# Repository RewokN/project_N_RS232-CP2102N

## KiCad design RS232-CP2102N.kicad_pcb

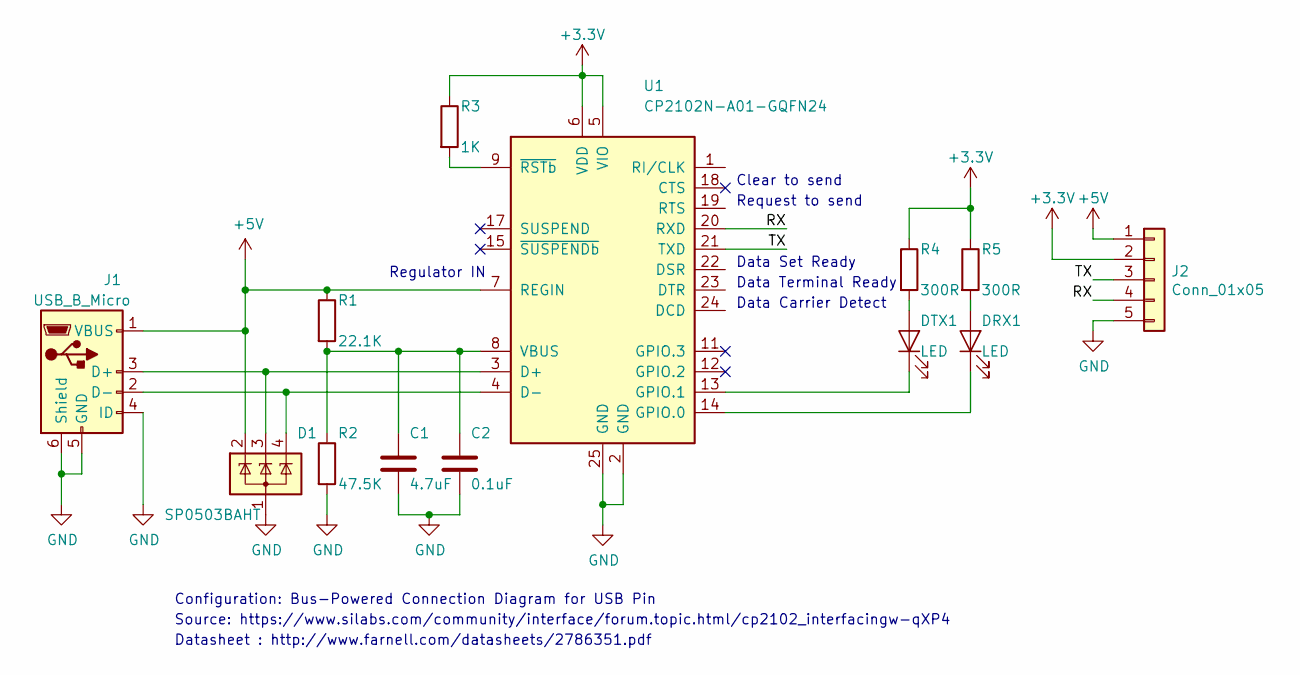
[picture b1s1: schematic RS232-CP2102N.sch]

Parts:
C1: 4.7uF; C_0805_2012Metric
C2: 0.1uF; C_0805_2012Metric
D1: SP0503BAHT; SOT-143
DRX1: LED; LED_0805_2012Metric
DTX1: LED; LED_0805_2012Metric
J1: USB_B_Micro; USB_Micro-B_Molex-105017-0001
J2: Conn_01x05; PinHeader_1x05_P2.54mm_Vertical
R1: 22.1K; R_0805_2012Metric
R2: 47.5K; R_0805_2012Metric
R3: 1K; R_0805_2012Metric
R4, R5: 300R; R_0805_2012Metric
U1: CP2102N-A01-GQFN24; QFN-24-1EP_4x4mm_P0.5mm_EP2.6x2.6mm

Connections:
+3V3: J2.2, R3.1, R4.1, R5.1, U1.5 (VIO), U1.6 (VDD)
+5V: D1.2 (K), J1.1 (VBUS), J2.1, R1.1, U1.7 (REGIN)
/RX: J2.4, U1.20 (RXD)
/TX: J2.3, U1.21 (TXD)
GND: C1.2, C2.2, D1.1 (A), J1.4 (ID), J1.5 (GND), J1.6 (Shield), J2.5, R2.2, U1.2 (GND), U1.25 (GND)
unnamed: C1.1, C2.1, R1.2, R2.1, U1.8 (VBUS)
unnamed: D1.3 (K), J1.3 (D+), U1.3 (D+)
unnamed: D1.4 (K), J1.2 (D-), U1.4 (D-)
unnamed: DRX1.1 (K), U1.14 (GPIO.0)
unnamed: DRX1.2 (A), R5.2
unnamed: DTX1.1 (K), U1.13 (GPIO.1)
unnamed: DTX1.2 (A), R4.2
unnamed: R3.2, U1.9 (~RSTb)

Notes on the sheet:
Clear to send
Request to send
Data Set Ready
Data Terminal Ready
Data Carrier Detect
Regulator IN
Configuration: Bus-Powered Connection Diagram for USB Pin
Source: https://www.silabs.com/community/interface/forum.topic.html/cp2102_interfacingw-qXP4
Datasheet : http://www.farnell.com/datasheets/2786351.pdf

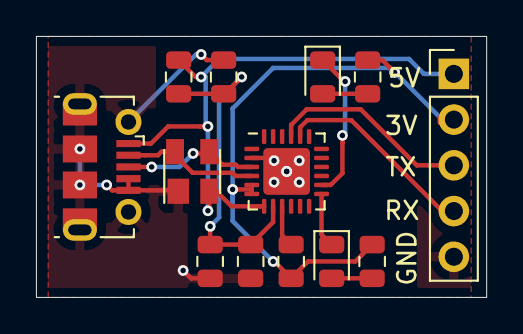
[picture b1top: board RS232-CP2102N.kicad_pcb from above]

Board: 2 copper layers, 25.0 x 14.5 mm, 13 parts (0 on the bottom side), 13 nets.

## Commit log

2019-09-15 Update RS232-CP2102N.sch-bak
